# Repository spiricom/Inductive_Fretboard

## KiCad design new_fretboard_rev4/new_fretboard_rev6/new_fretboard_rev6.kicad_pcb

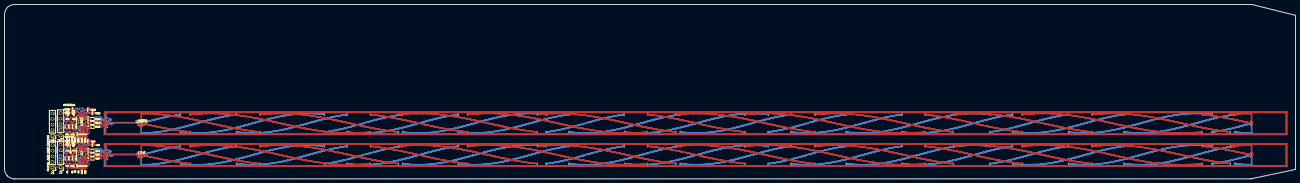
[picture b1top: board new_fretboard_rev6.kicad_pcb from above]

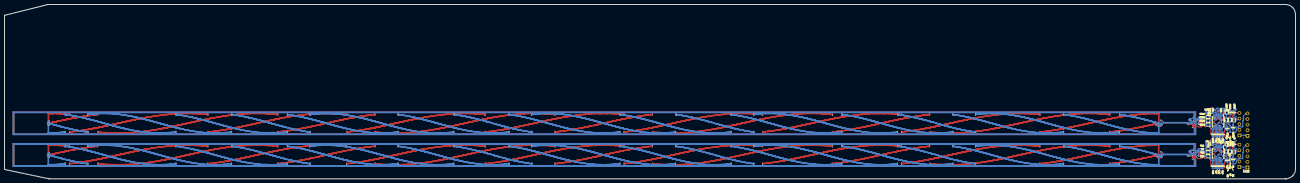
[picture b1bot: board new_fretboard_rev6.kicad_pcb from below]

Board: 4 copper layers, 585.0 x 79.0 mm, 96 parts (46 on the bottom side), 61 nets.

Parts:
C1, C2, C3, C4, C301, C302, C303, C304: 6.8nF; C_0603
C5, C6, C13, C14, C305, C306, C313, C314: 100nF; C_0603
C7, C8, C307, C308: 1000pF; C_0603
C9, C10, C309, C310: 470nF; C_0603
C11, C12, C311, C312: 1uF; C_0603
C15, C16, C17, C18, C315, C316, C317, C318: 10pF; C_0603
C19, C20, C21, C22, C319, C320, C321, C322: 680PF; C_0603
J1, J301: Conn_01x06; PinHeader_1x05_P2.54mm_Vertical
J2, J302: Conn_01x05; PinHeader_1x05_P2.54mm_Vertical
L1, L2, L3, L4, L5, L6, L7, L8, L301, L302, L303, L304, L305, L306, L307, L308: PCB L; jumper_tiny
R1, R2, R301, R302: 221R; R_0603
R3, R4, R5, R6, R303, R304, R305, R306: 10k; R_0603
R7, R8, R307, R308: 4.7R; R_0603
R9, R10, R11, R12, R13, R14, R309, R310, R311, R312, R313, R314: 10R; R_0603
U1, U2, U301, U302: LX3302AQPW_TSSOP-14; TSSOP-14_4.4x5mm_P0.65mm

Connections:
/ch1/COS_A: L7.1, R13.2
/ch1/COS_A_PRE_RES: C18.2, R13.1, U2.10 (CL2)
/ch1/COS_B: L5.1, R11.2
/ch1/COS_B_PRE_RES: C17.2, R11.1, U1.10 (CL2)
/ch1/IO1_A: J2.5, R4.1, U2.7 (IO1)
/ch1/IO1_B: J1.5, R3.1, U1.7 (IO1)
/ch1/IO2_A: C4.2, R2.2, R6.1, U2.6 (IO2)
/ch1/IO2_A_FILT: C2.2, J2.4, R2.1
/ch1/IO2_B: C3.2, R1.2, R5.1, U1.6 (IO2)
/ch1/IO2_B_FILT: C1.2, J1.4, R1.1
/ch1/IO3_A: J2.3, U2.3 (IO3)
/ch1/IO3_B: J1.3, U1.3 (IO3)
/ch1/OSC_CCW_A: C22.2, L4.1, U2.12 (OSC2)
/ch1/OSC_CCW_B: C20.2, L3.1, U1.12 (OSC2)
/ch1/OSC_CW_A: C21.2, L2.1, U2.13 (OSC1)
/ch1/OSC_CW_B: C19.2, L1.1, U1.13 (OSC1)
/ch1/OSC_RTN_A: L2.2, L4.2, R10.1
/ch1/OSC_RTN_B: L1.2, L3.2, R9.1
/ch1/SIN_A: L8.1, R14.2
/ch1/SIN_A_PRE_RES: C16.2, R14.1, U2.8 (CL1)
/ch1/SIN_B: L6.1, R12.2
/ch1/SIN_B_PRE_RES: C15.2, R12.1, U1.8 (CL1)
/ch1/SUB_A: C14.1, U2.11 (SUB)
/ch1/SUB_B: C13.1, U1.11 (SUB)
/ch1/VDD1_A: C12.2, C14.2, U2.5 (VDD)
/ch1/VDD1_B: C11.2, C13.2, U1.5 (VDD)
/ch1/VIN1_A: C8.2, C10.2, R4.2, R6.2, R8.2, R10.2, U2.4 (VIN)
/ch1/VIN1_B: C7.2, C9.2, R3.2, R5.2, R7.2, R9.2, U1.4 (VIN)
/ch1/VIN_A: C6.2, J2.2, R8.1
/ch1/VIN_B: C5.2, J1.2, R7.1
/ch2/COS_A: L307.1, R313.2
/ch2/COS_A_PRE_RES: C318.2, R313.1, U302.10 (CL2)
/ch2/COS_B: L305.1, R311.2
/ch2/COS_B_PRE_RES: C317.2, R311.1, U301.10 (CL2)
/ch2/IO1_A: J302.5, R304.1, U302.7 (IO1)
/ch2/IO1_B: J301.5, R303.1, U301.7 (IO1)
/ch2/IO2_A: C304.2, R302.2, R306.1, U302.6 (IO2)
/ch2/IO2_A_FILT: C302.2, J302.4, R302.1
/ch2/IO2_B: C303.2, R301.2, R305.1, U301.6 (IO2)
/ch2/IO2_B_FILT: C301.2, J301.4, R301.1
/ch2/IO3_A: J302.3, U302.3 (IO3)
/ch2/IO3_B: J301.3, U301.3 (IO3)
/ch2/OSC_CCW_A: C322.2, L304.1, U302.12 (OSC2)
/ch2/OSC_CCW_B: C320.2, L303.1, U301.12 (OSC2)
/ch2/OSC_CW_A: C321.2, L302.1, U302.13 (OSC1)
/ch2/OSC_CW_B: C319.2, L301.1, U301.13 (OSC1)
/ch2/OSC_RTN_A: L302.2, L304.2, R310.1
/ch2/OSC_RTN_B: L301.2, L303.2, R309.1
/ch2/SIN_A: L308.1, R314.2
/ch2/SIN_A_PRE_RES: C316.2, R314.1, U302.8 (CL1)
/ch2/SIN_B: L306.1, R312.2
/ch2/SIN_B_PRE_RES: C315.2, R312.1, U301.8 (CL1)
/ch2/SUB_A: C314.1, U302.11 (SUB)
/ch2/SUB_B: C313.1, U301.11 (SUB)
/ch2/VDD1_A: C312.2, C314.2, U302.5 (VDD)
/ch2/VDD1_B: C311.2, C313.2, U301.5 (VDD)
/ch2/VIN1_A: C308.2, C310.2, R304.2, R306.2, R308.2, R310.2, U302.4 (VIN)
/ch2/VIN1_B: C307.2, C309.2, R303.2, R305.2, R307.2, R309.2, U301.4 (VIN)
/ch2/VIN_A: C306.2, J302.2, R308.1
/ch2/VIN_B: C305.2, J301.2, R307.1
GND1: C1.1, C2.1, C3.1, C4.1, C5.1, C6.1, C7.1, C8.1, C9.1, C10.1, C11.1, C12.1, C15.1, C16.1, C17.1, C18.1, C19.1, C20.1, C21.1, C22.1, C301.1, C302.1, C303.1, C304.1, C305.1, C306.1, C307.1, C308.1, C309.1, C310.1, C311.1, C312.1, C315.1, C316.1, C317.1, C318.1, C319.1, C320.1, C321.1, C322.1, J1.1, J2.1, J301.1, J302.1, L5.2, L6.2, L7.2, L8.2, L305.2, L306.2, L307.2, L308.2, U1.2 (GND), U1.9 (GNDCL), U2.2 (GND), U2.9 (GNDCL), U301.2 (GND), U301.9 (GNDCL), U302.2 (GND), U302.9 (GNDCL)

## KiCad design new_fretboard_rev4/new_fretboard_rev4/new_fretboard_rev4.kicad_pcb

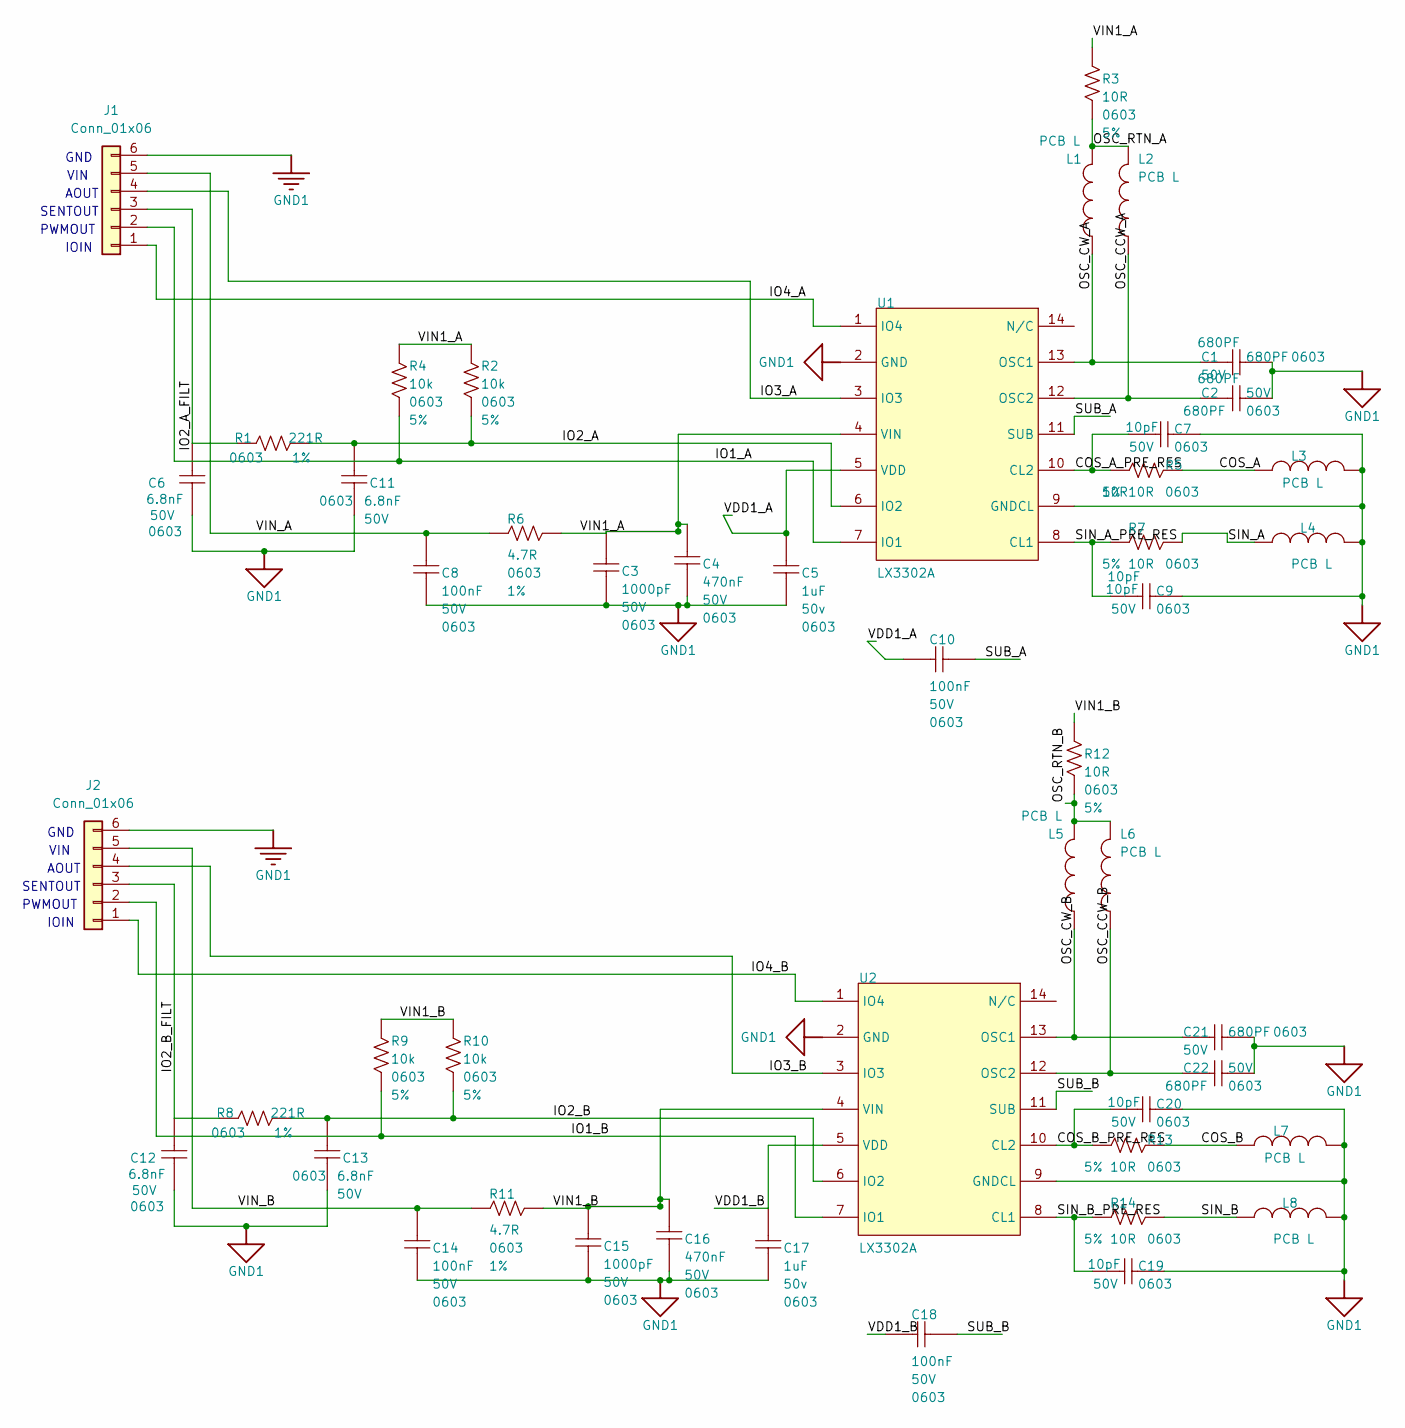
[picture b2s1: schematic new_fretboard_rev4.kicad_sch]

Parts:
C1, C2, C21, C22: 680PF; C_0603; VOLTAGE 50V; TOLERANCE ±10%; MANUFACTURER PART NUMBE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 C0603C681K5GAC7867
C3, C15: 1000pF; C_0603; VOLTAGE 50V; TOLERANCE 10%; MANUFACTURER PART NUMBE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 C1608X7R1H102K
C4, C16: 470nF; C_0603; VOLTAGE 50V; TOLERANCE 10%; MANUFACTURER PART NUMBE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 UMK107B7474KA-TR
C5, C17: 1uF; C_0603; VOLTAGE 50v; TOLERANCE 10%; MANUFACTURER PART NUMBE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 UMK107AB7105KA-T
C6, C11, C12, C13: 6.8nF; C_0603; VOLTAGE 50V; TOLERANCE 5%; MANUFACTURER PART NUMBE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 CGA3E2C0G1H682J080AA
C7, C9, C19, C20: 10pF; C_0603; VOLTAGE 50V; TOLERANCE 10%; MANUFACTURER PART NUMBE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 C0402C100K5RAC7867
C8, C10, C14, C18: 100nF; C_0603; VOLTAGE 50V; TOLERANCE 10%; MANUFACTURER PART NUMBE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 06035C104K4T2A
J1, J2: Conn_01x06; PinHeader_1x06_P2.54mm_Vertical; Part Number 1-0601FBV0T
L1, L2, L3, L4, L5, L6, L7, L8: PCB L; jumper_tiny
R1, R8: 221R; R_0603; TOLERANCE 1%; VOLTAGE 75V; MANUFACTURER PART NUMBE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 ERJ-3EKF2210V
R2, R4, R9, R10: 10k; R_0603; TOLERANCE 5%; VOLTAGE 75V; MANUFACTURER PART NUMBE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 ERJ-3GEYJ103V
R3, R5, R7, R12, R13, R14: 10R; R_0603; TOLERANCE 5%; VOLTAGE 75V; MANUFACTURER PART NUMBE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 ERJ-3GEYJ100V
R6, R11: 4.7R; R_0603; TOLERANCE 1%; MANUFACTURER PART NUMBE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 ERJ-3RQF4R7V
U1, U2: LX3302AQPW_TSSOP-14; TSSOP-14_4.4x5mm_P0.65mm; MANUFACTURER PART NUMBE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 LX3302AQPW

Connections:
/COS_A: L3.1, R5.2
/COS_A_PRE_RES: C7.2, R5.1, U1.10 (CL2)
/COS_B: L7.1, R13.2
/COS_B_PRE_RES: C20.2, R13.1, U2.10 (CL2)
/IO1_A: J1.2, R4.1, U1.7 (IO1)
/IO1_B: J2.2, R9.1, U2.7 (IO1)
/IO2_A: C11.2, R1.2, R2.1, U1.6 (IO2)
/IO2_A_FILT: C6.2, J1.3, R1.1
/IO2_B: C13.2, R8.2, R10.1, U2.6 (IO2)
/IO2_B_FILT: C12.2, J2.3, R8.1
/IO3_A: J1.4, U1.3 (IO3)
/IO3_B: J2.4, U2.3 (IO3)
/IO4_A: J1.1, U1.1 (IO4)
/IO4_B: J2.1, U2.1 (IO4)
/OSC_CCW_A: C2.2, L2.1, U1.12 (OSC2)
/OSC_CCW_B: C22.2, L6.1, U2.12 (OSC2)
/OSC_CW_A: C1.2, L1.1, U1.13 (OSC1)
/OSC_CW_B: C21.2, L5.1, U2.13 (OSC1)
/OSC_RTN_A: L1.2, L2.2, R3.1
/OSC_RTN_B: L5.2, L6.2, R12.1
/SIN_A: L4.1, R7.2
/SIN_A_PRE_RES: C9.2, R7.1, U1.8 (CL1)
/SIN_B: L8.1, R14.2
/SIN_B_PRE_RES: C19.2, R14.1, U2.8 (CL1)
/SUB_A: C10.1, U1.11 (SUB)
/SUB_B: C18.1, U2.11 (SUB)
/VDD1_A: C5.2, C10.2, U1.5 (VDD)
/VDD1_B: C17.2, C18.2, U2.5 (VDD)
/VIN1_A: C3.2, C4.2, R2.2, R3.2, R4.2, R6.2, U1.4 (VIN)
/VIN1_B: C15.2, C16.2, R9.2, R10.2, R11.2, R12.2, U2.4 (VIN)
/VIN_A: C8.2, J1.5, R6.1
/VIN_B: C14.2, J2.5, R11.1
GND1: C1.1, C2.1, C3.1, C4.1, C5.1, C6.1, C7.1, C8.1, C9.1, C11.1, C12.1, C13.1, C14.1, C15.1, C16.1, C17.1, C19.1, C20.1, C21.1, C22.1, J1.6, J2.6, L3.2, L4.2, L7.2, L8.2, U1.2 (GND), U1.9 (GNDCL), U2.2 (GND), U2.9 (GNDCL)

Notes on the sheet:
VIN
IOIN
AOUT
GND
SENTOUT
PWMOUT

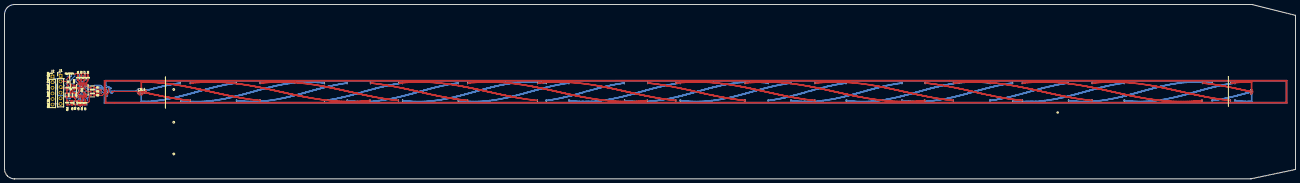
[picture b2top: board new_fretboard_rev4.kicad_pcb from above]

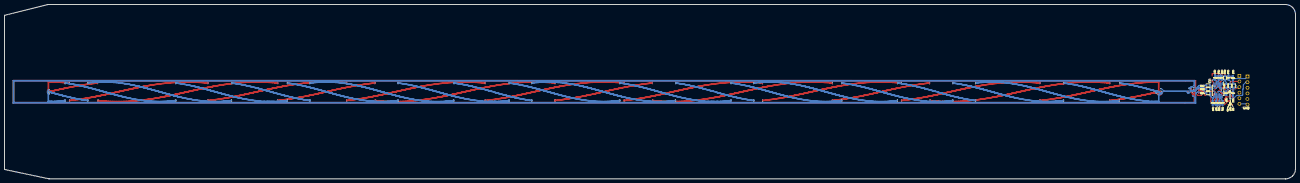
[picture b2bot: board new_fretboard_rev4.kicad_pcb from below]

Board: 4 copper layers, 585.0 x 79.0 mm, 48 parts (23 on the bottom side), 33 nets.
